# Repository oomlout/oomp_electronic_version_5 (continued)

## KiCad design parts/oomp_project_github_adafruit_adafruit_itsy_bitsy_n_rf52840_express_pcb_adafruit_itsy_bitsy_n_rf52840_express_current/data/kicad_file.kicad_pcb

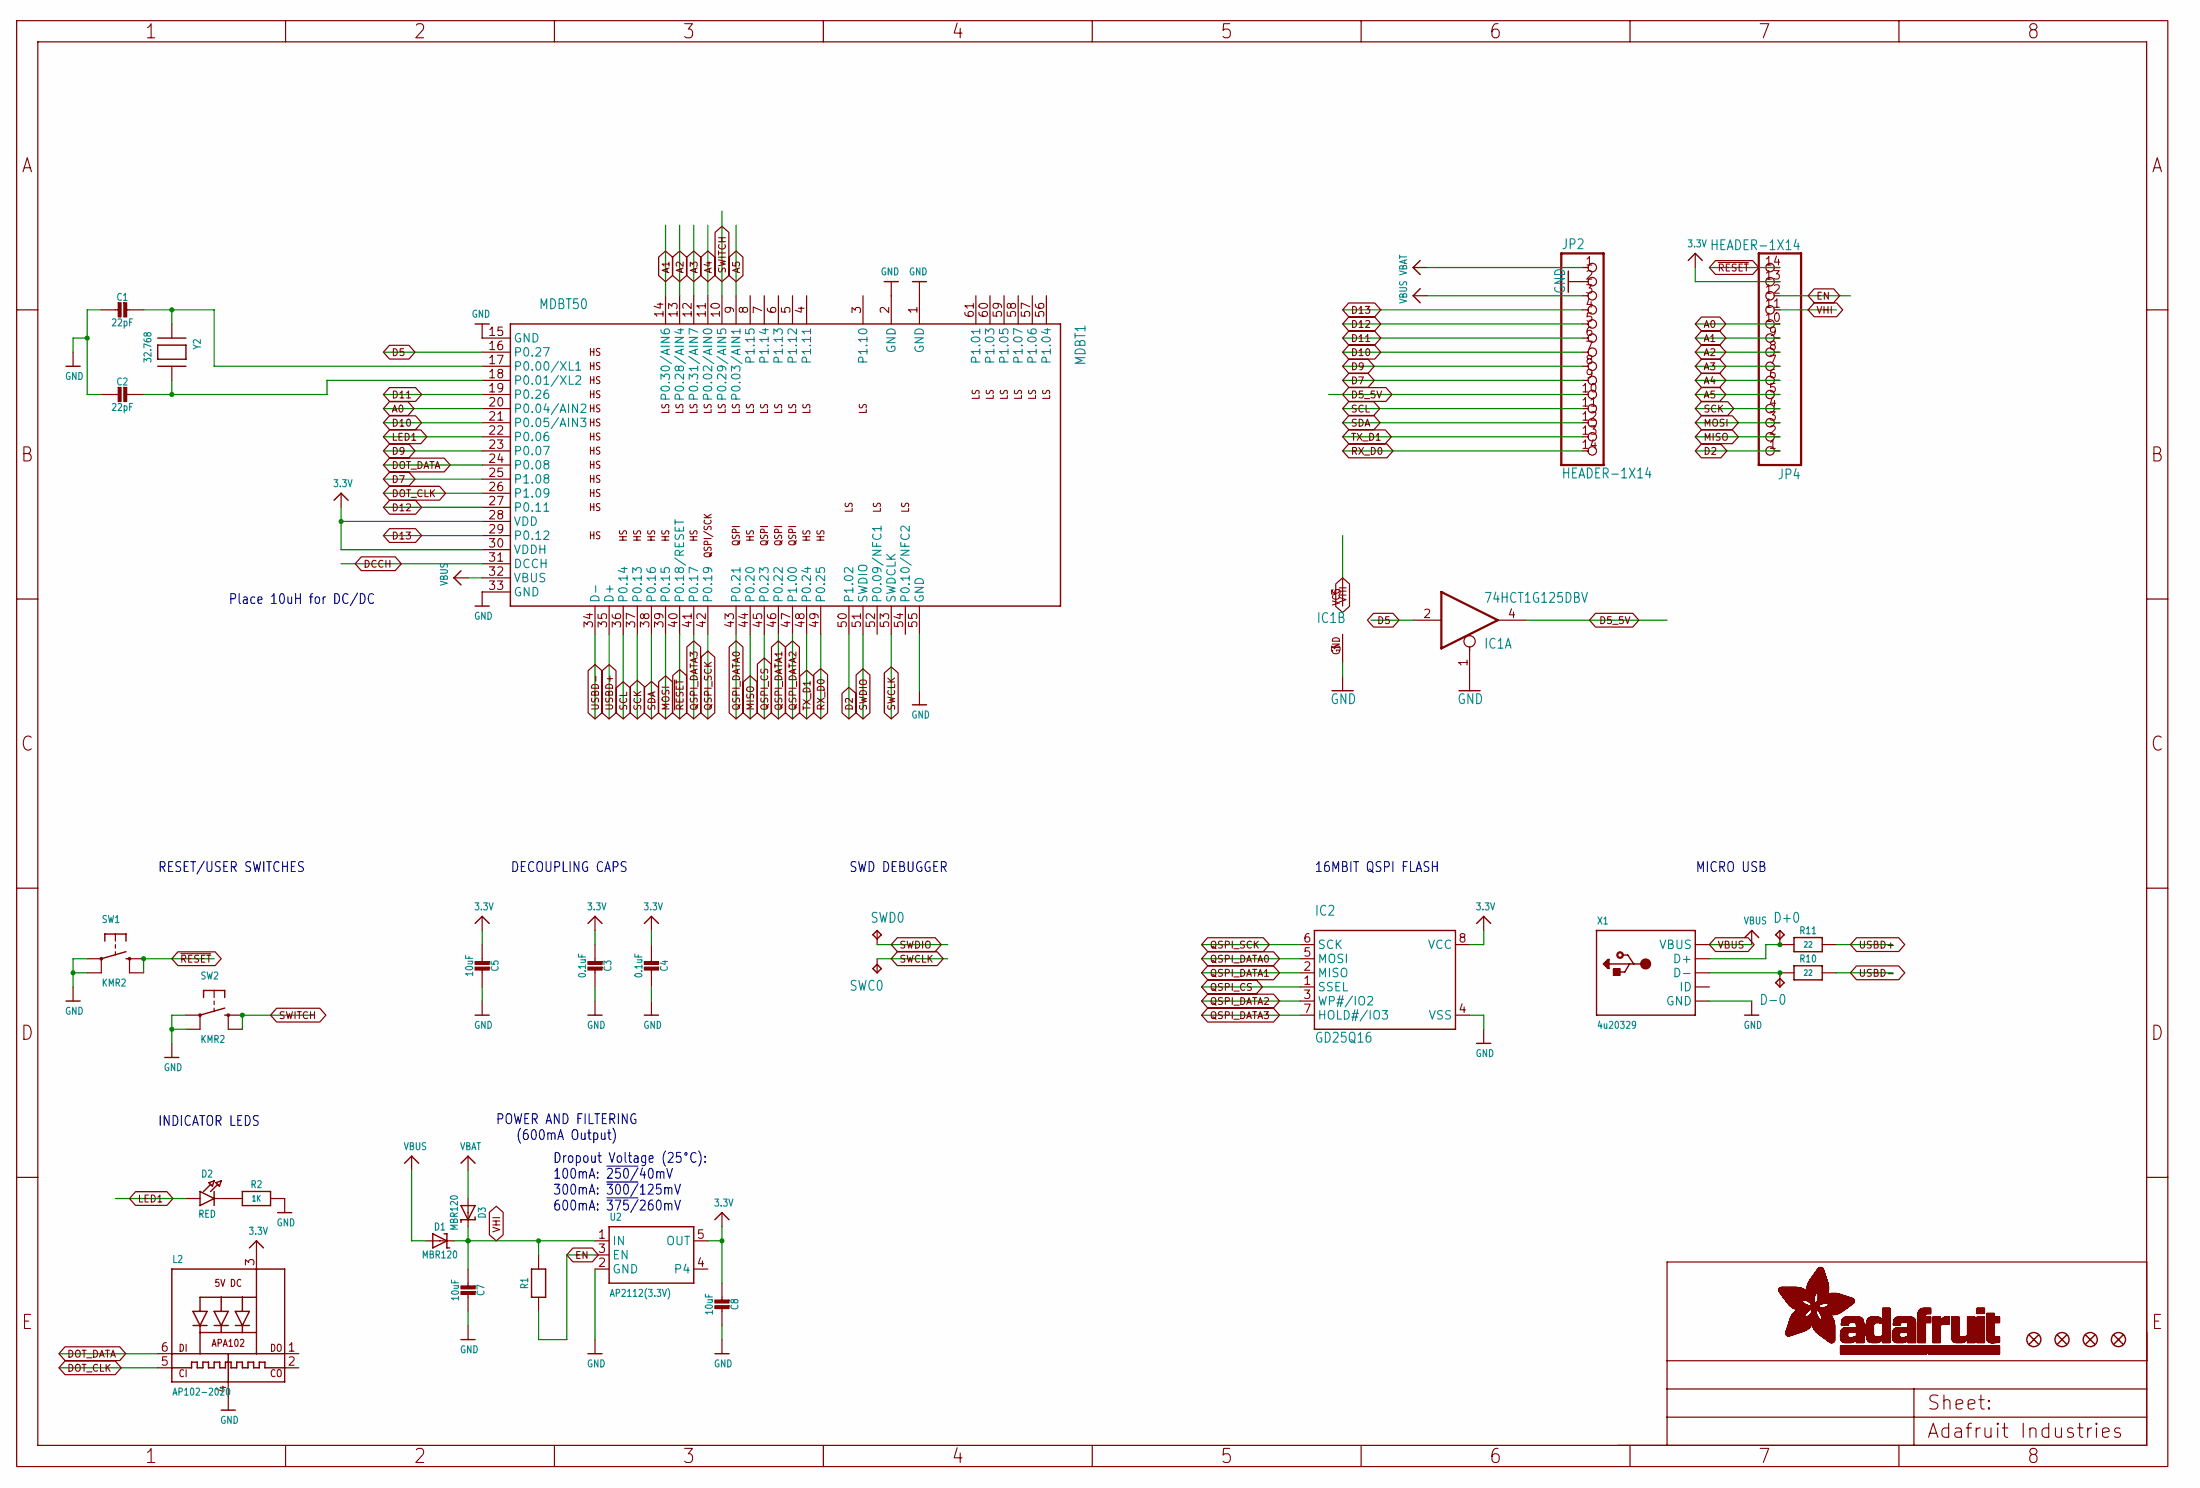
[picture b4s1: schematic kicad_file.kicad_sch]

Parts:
C1, C2: 22pF; _0603MP
C3, C4: 0.1uF; 0603-NO
C5, C7, C8: 10uF; 0805-NO
D1, D3: MBR120; SOD-123
D2: RED; CHIPLED_0805_NOOUTLINE
D+0: TPTP10R; TP10R
D-0: TPTP10R; TP10R
FID1, FID2, FID3, FID4: FIDUCIAL_1MM
IC1: 74HCT1G125DBV; SOT23-5
IC2: GD25Q16; USON8
JP2, JP4: HEADER-1X14; 1X14_ROUND70
L2: AP102-2020; APA102_2020
MDBT1: MDBT50
R1: 10K; 0603-NO
R2: 1K; 0603-NO
R10, R11: 22; 0603-NO
SW1, SW2: KMR2; BTN_KMR2_4.6X2.8
SWC0: TPTP13R; TP13R
SWD0: TPTP13R; TP13R
U2: AP2112(3.3V); SOT23-5
X1: 4u20329; 4UCONN_20329_V2
Y2: 32.768; XTAL3215

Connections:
3.3V: C3.2, C4.2, C5.2, C8.2, IC2.8 (VCC), JP4.13, L2.3 (VDD), MDBT1.28 (VDD), MDBT1.30 (VDDH), U2.5 (OUT)
A0: JP4.10, MDBT1.20 (P0.04/AIN2)
A1: JP4.9, MDBT1.14 (P0.30/AIN6)
A2: JP4.8, MDBT1.13 (P0.28/AIN4)
A3: JP4.7, MDBT1.12 (P0.31/AIN7)
A4: JP4.6, MDBT1.11 (P0.02/AIN0)
A5: JP4.5, MDBT1.9 (P0.03/AIN1)
D2: JP4.1, MDBT1.50 (P1.02)
D5: IC1.2 (I), MDBT1.16 (P0.27)
D5_5V: IC1.4 (O), JP2.10
D7: JP2.9, MDBT1.25 (P1.08)
D9: JP2.8, MDBT1.23 (P0.07)
D10: JP2.7, MDBT1.21 (P0.05/AIN3)
D11: JP2.6, MDBT1.19 (P0.26)
D12: JP2.5, MDBT1.27 (P0.11)
D13: JP2.4, MDBT1.29 (P0.12)
D+: D+0.TP, R11.1, X1.D+
D-: D-0.TP, R10.1, X1.D-
DCCH: MDBT1.31 (DCCH)
DOT_CLK: L2.5 (CKI), MDBT1.26 (P1.09)
DOT_DATA: L2.6 (DI), MDBT1.24 (P0.08)
EN: JP4.12, R1.1, U2.3 (EN)
GND: C1.2, C2.2, C3.1, C4.1, C5.1, C7.1, C8.1, IC1.1 (OE), IC1.3 (GND), IC2.4 (VSS), JP2.2, L2.4 (GND), MDBT1.1 (GND), MDBT1.2 (GND), MDBT1.15 (GND), MDBT1.33 (GND), MDBT1.55 (GND), R2.2, SW1.A, SW1.A' (P1), SW2.A, SW2.A' (P1), U2.2 (GND), X1.BASE@1 (GND), X1.BASE@2 (GND), X1.GND, X1.SPRT@1 (GND), X1.SPRT@2 (GND), X1.SPRT@3 (GND), X1.SPRT@4 (GND)
LED1: D2.A, MDBT1.22 (P0.06)
MISO: JP4.2, MDBT1.44 (P0.20)
MOSI: JP4.3, MDBT1.39 (P0.15)
unnamed: D2.C, R2.1
unnamed: C1.1, MDBT1.17 (P0.00/XL1), Y2.P$1
unnamed: C2.1, MDBT1.18 (P0.01/XL2), Y2.P$2
QSPI_CS: IC2.1 (SSEL), MDBT1.45 (P0.23)
QSPI_DATA0: IC2.5 (MOSI), MDBT1.43 (P0.21)
QSPI_DATA1: IC2.2 (MISO), MDBT1.46 (P0.22)
QSPI_DATA2: IC2.3 (WP#/IO2), MDBT1.47 (P1.00)
QSPI_DATA3: IC2.7 (HOLD#/IO3), MDBT1.41 (P0.17)
QSPI_SCK: IC2.6 (SCK), MDBT1.42 (P0.19)
RX_D0: JP2.14, MDBT1.49 (P0.25)
SCK: JP4.4, MDBT1.37 (P0.13)
SCL: JP2.11, MDBT1.36 (P0.14)
SDA: JP2.12, MDBT1.38 (P0.16)
SWCLK: MDBT1.53 (SWDCLK), SWC0.TP
SWDIO: MDBT1.51 (SWDIO), SWD0.TP
SWITCH: MDBT1.10 (P0.29/AIN5), SW2.B (S), SW2.B' (S1)
TX_D1: JP2.13, MDBT1.48 (P0.24)
USBD+: MDBT1.35 (D+), R11.2
USBD-: MDBT1.34 (D-), R10.2
VBAT: D3.A, JP2.1
VBUS: D1.A, JP2.3, MDBT1.32 (VBUS), X1.VBUS
VHI: C7.2, D1.C, D3.C, IC1.5 (VCC), JP4.11, R1.2, U2.1 (IN)
~RESET: JP4.14, MDBT1.40 (P0.18/RESET), SW1.B (S), SW1.B' (S1)

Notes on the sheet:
Place 10uH for DC/DC
MICRO USB
16MBIT QSPI FLASH
SWD DEBUGGER
DECOUPLING CAPS
POWER AND FILTERING (600mA Output)
RESET/USER SWITCHES
INDICATOR LEDS
Dropout Voltage (25°C): 100mA: ~{250/}40mV 300mA: ~{300/}125mV 600mA: ~{375/}260mV

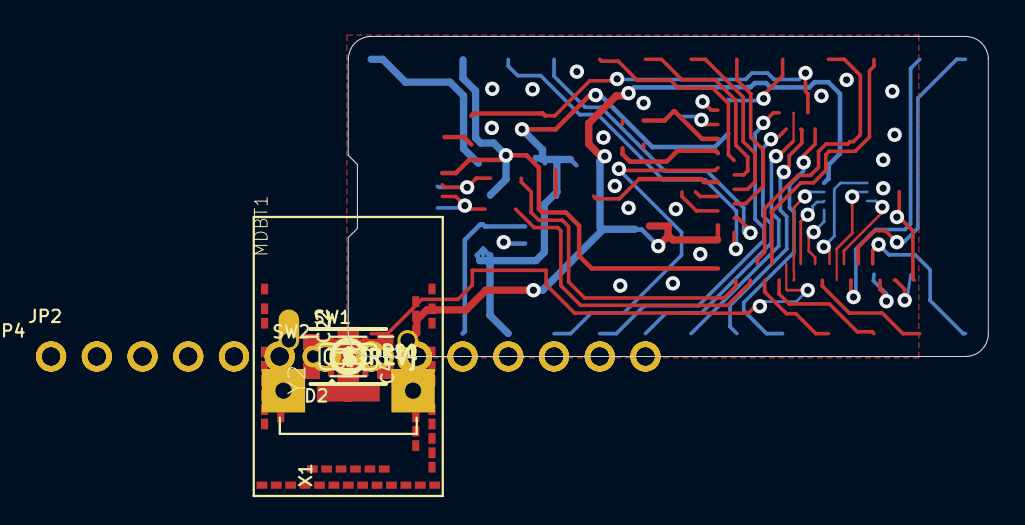
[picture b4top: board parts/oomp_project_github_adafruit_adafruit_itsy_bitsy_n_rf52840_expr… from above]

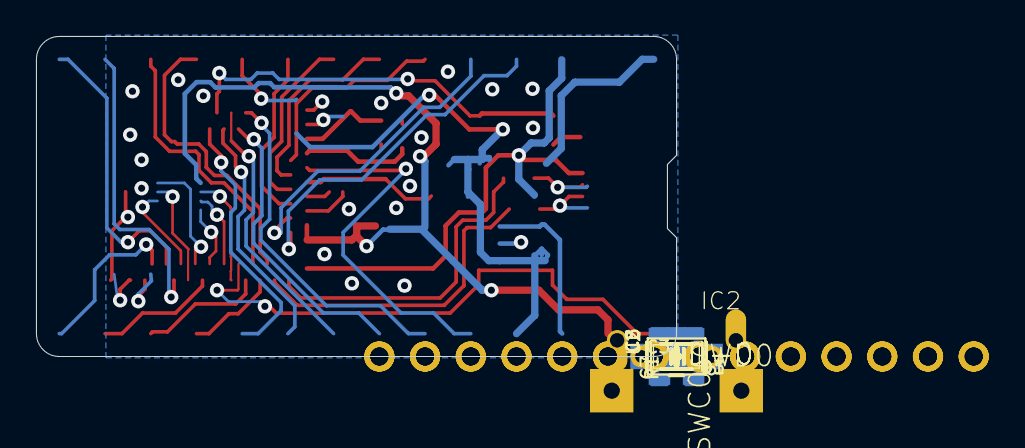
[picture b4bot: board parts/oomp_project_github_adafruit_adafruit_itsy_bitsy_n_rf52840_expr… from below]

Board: 2 copper layers, 35.6 x 17.8 mm, 36 parts (17 on the bottom side), 48 nets.

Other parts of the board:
U$12: ITSYNRF52840_TOP
U$14: ITSYNRF52840_BOT
U$15: PCBFEAT-REV-040

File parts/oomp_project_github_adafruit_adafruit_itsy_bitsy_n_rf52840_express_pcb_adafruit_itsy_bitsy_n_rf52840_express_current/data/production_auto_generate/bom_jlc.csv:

Comment,Designator,Footprint,LCSC Part #
,"JP2,JP4",Adafruit ItsyBitsy nRF52840 Express-import-fps:1X14_ROUND70,C2905490
,U$14,Adafruit ItsyBitsy nRF52840 Express-import-fps:ITSYNRF52840_BOT,
,U$12,Adafruit ItsyBitsy nRF52840 Express-import-fps:ITSYNRF52840_TOP,
,U$15,Adafruit ItsyBitsy nRF52840 Express-import-fps:PCBFEAT-REV-040,
0.1uF,"C3,C4",Adafruit ItsyBitsy nRF52840 Express-import-fps:0603-NO,C14663
10K,R1,Adafruit ItsyBitsy nRF52840 Express-import-fps:0603-NO,C98220
10uF,"C5,C7,C8",Adafruit ItsyBitsy nRF52840 Express-import-fps:0805-NO,
1K,R2,Adafruit ItsyBitsy nRF52840 Express-import-fps:0603-NO,C2907002
22,"R10,R11",Adafruit ItsyBitsy nRF52840 Express-import-fps:0603-NO,C23345
22pF,"C1,C2",Adafruit ItsyBitsy nRF52840 Express-import-fps:_0603MP,C105620
32.768,Y2,Adafruit ItsyBitsy nRF52840 Express-import-fps:XTAL3215,
4u20329,X1,Adafruit ItsyBitsy nRF52840 Express-import-fps:4UCONN_20329_V2,
74HCT1G125DBV,IC1,Adafruit ItsyBitsy nRF52840 Express-import-fps:SOT23-5,
AP102-2020,L2,Adafruit ItsyBitsy nRF52840 Express-import-fps:APA102_2020,
AP2112(3.3V),U2,Adafruit ItsyBitsy nRF52840 Express-import-fps:SOT23-5,
GD25Q16,IC2,Adafruit ItsyBitsy nRF52840 Express-import-fps:USON8,
KMR2,"SW1,SW2",Adafruit ItsyBitsy nRF52840 Express-import-fps:BTN_KMR2_4.6X2.8,
MBR120,"D1,D3",Adafruit ItsyBitsy nRF52840 Express-import-fps:SOD-123,
MDBT50,MDBT1,Adafruit ItsyBitsy nRF52840 Express-import-fps:MDBT50,
RED,D2,Adafruit ItsyBitsy nRF52840 Express-import-fps:CHIPLED_0805_NOOUTLINE,
TPTP10R,"D+0,D-0",Adafruit ItsyBitsy nRF52840 Express-import-fps:TP10R,
TPTP13R,"SWC0,SWD0",Adafruit ItsyBitsy nRF52840 Express-import-fps:TP13R,
